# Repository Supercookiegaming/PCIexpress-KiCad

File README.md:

# PCIexpress-KiCad
PCI Express™ libraries and templates for KiCad
Made using guidelines from PCI Express™ Card Electromechanical Specification Rev. 4.0 Version 0.9 and PCI Express™ M.2 Specification Revision 1.0

Updated for KiCad 9.0.1

### Contents
**Templates:**
* M.2 A Key 22/30mm width, 30/42/60/80/110mm length
* M.2 B Key 22/30mm width, 30/42/60/80/110mm length
* M.2 M Key 22/30mm width, 30/42/60/80/110mm length
* M.2 E Key 22/30mm width, 30/42/60/80/110mm length
* M.2 A+E Key 22/30mm width, 30/42/60/80/110mm length
* M.2 B+M Key 22/30mm width, 30/42/60/80/110mm length
* x1 cards: full size, half length, low profile
* x2 cards: full size, half length, low profile
* x4 cards: full size, half length, low profile
* x8 cards: full size, half length, low profile
* x16 cards: full size, half length, low profile

**Symbols:**
* A Key M.2
* B Key M.2
* C Key M.2
* D Key M.2
* E Key M.2
* F Key M.2
* G Key M.2
* H Key M.2
* J Key M.2
* K Key M.2
* L Key M.2
* M Key M.2
* A+E Key M.2
* B+M Key M.2
* x1
* x2
* x4
* x8
* x16
* Bracket

**Footprints:**
* A Key M.2 with multiple card outlines
* B Key M.2 with multiple card outlines
* C Key M.2 with multiple card outlines
* D Key M.2 with multiple card outlines
* E Key M.2 with multiple card outlines
* F Key M.2 with multiple card outlines
* G Key M.2 with multiple card outlines
* H Key M.2 with multiple card outlines
* J Key M.2 with multiple card outlines
* K Key M.2 with multiple card outlines
* L Key M.2 with multiple card outlines
* M Key M.2 with multiple card outlines
* A+E Key M.2 with multiple card outlines
* B+M Key M.2 with multiple card outlines
* M.2 Mounting Pad
* x1 with multiple card outlines
* x2 with multiple card outlines
* x4 with multiple card outlines
* x8 with multiple card outlines
* x16 with multiple card outlines
* Full height bracket (with 3D model)
* Low profile bracket (with 3D model)
* Low profile to full height adapter bracker (with 3D model)

**Notes:**
* Transmit and Recieve pairs on M.2 Symbols are from the perspective of module not the host.
* Transmit and Recieve pairs on PCIe symbols are from the perspective of module not the host. 
* Triple check the pinout on your specific M.2 socket to ensure correct wiring.

### License
This documentation describes Open Hardware and is licensed under the CERN OHL v.1.2.

You may redistribute and modify this documentation under the terms of the CERN OHL v.1.2. (http://ohwr.org/cernohl). This documentation is distributed WITHOUT ANY EXPRESS OR IMPLIED WARRANTY, INCLUDING OF MERCHANTABILITY, SATISFACTORY QUALITY AND FITNESS FOR A PARTICULAR PURPOSE. Please see the CERN OHL v.1.2 for applicable conditions.

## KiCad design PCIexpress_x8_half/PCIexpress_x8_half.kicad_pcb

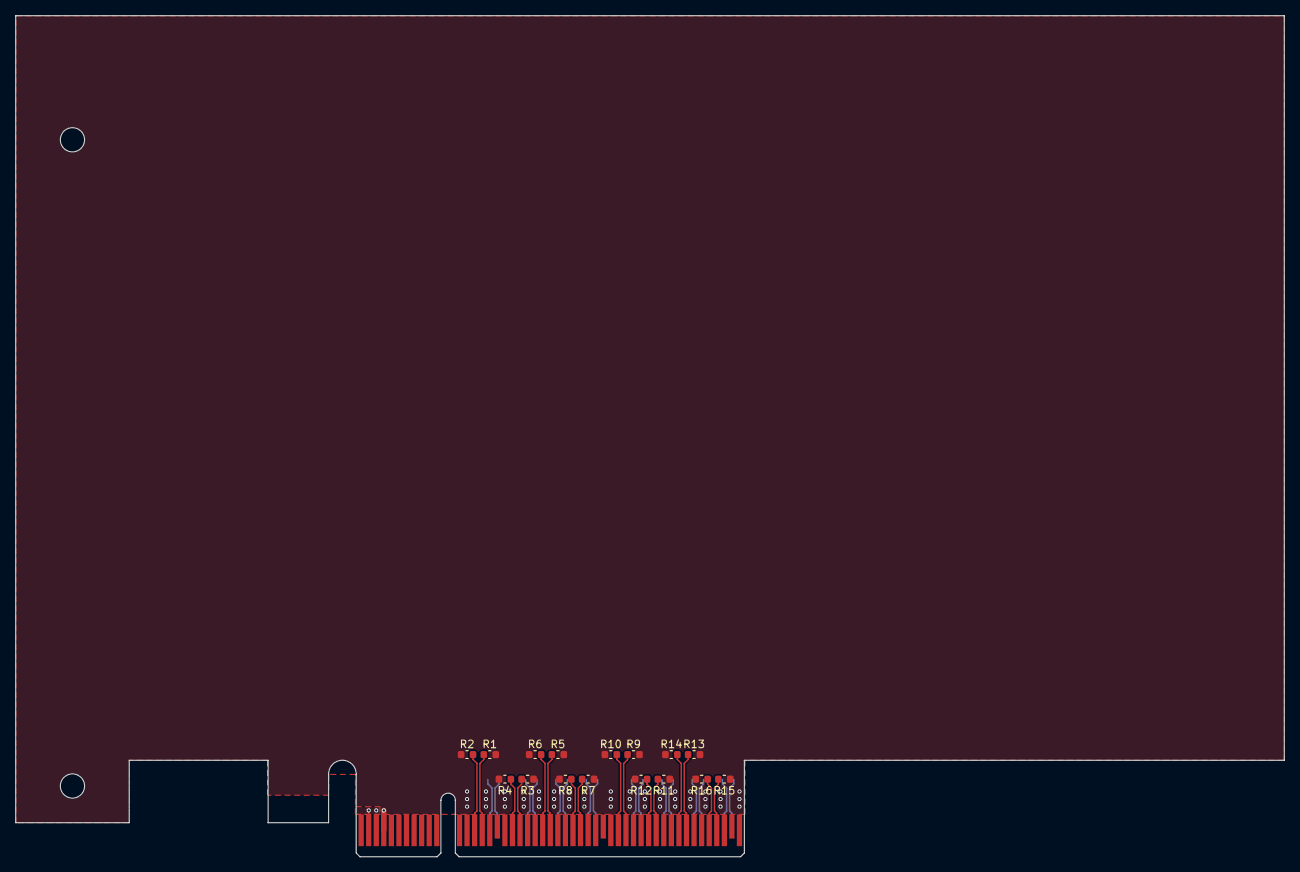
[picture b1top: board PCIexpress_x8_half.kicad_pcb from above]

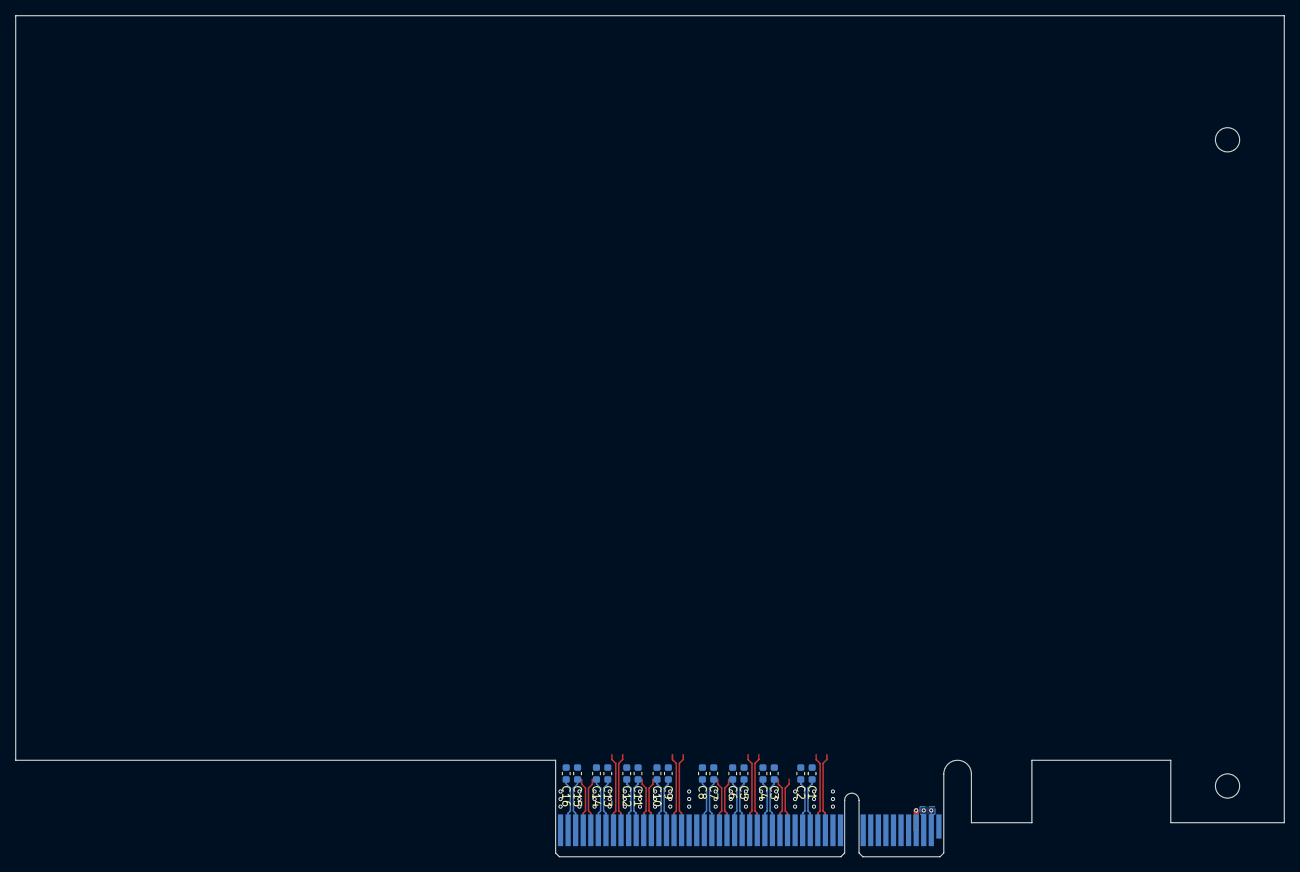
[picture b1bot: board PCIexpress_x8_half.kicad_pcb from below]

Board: 4 copper layers, 167.7 x 111.2 mm, 34 parts (16 on the bottom side), 35 nets.

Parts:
C1, C2, C3, C4, C5, C6, C7, C8, C9, C10, C11, C12, C13, C14, C15, C16: 100n; C_0603_1608Metric
J1: PCIexpress_bracket; PCIexpress_bracket_full
J2: PCIexpress_x8
R1, R2, R3, R4, R5, R6, R7, R8, R9, R10, R11, R12, R13, R14, R15, R16: 49.9; R_0603_1608Metric

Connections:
+3V3: J2.A9, J2.A10, J2.B8
+12V: J2.A2, J2.A3, J2.B1, J2.B2, J2.B3
/PCIexpress_connector/_PER0_N: C2.1, J2.A17
/PCIexpress_connector/_PER0_P: C1.2, J2.A16
/PCIexpress_connector/_PER1_N: C4.1, J2.A22
/PCIexpress_connector/_PER1_P: C3.2, J2.A21
/PCIexpress_connector/_PER2_N: C6.1, J2.A26
/PCIexpress_connector/_PER2_P: C5.2, J2.A25
/PCIexpress_connector/_PER3_N: C8.1, J2.A30
/PCIexpress_connector/_PER3_P: C7.2, J2.A29
/PCIexpress_connector/_PER4_N: C10.1, J2.A36
/PCIexpress_connector/_PER4_P: C9.2, J2.A35
/PCIexpress_connector/_PER5_N: C12.1, J2.A40
/PCIexpress_connector/_PER5_P: C11.2, J2.A39
/PCIexpress_connector/_PER6_N: C14.1, J2.A44
/PCIexpress_connector/_PER6_P: C13.2, J2.A43
/PCIexpress_connector/_PER7_N: C16.1, J2.A48
/PCIexpress_connector/_PER7_P: C15.2, J2.A47
/PET0_N: J2.B15, R1.1
/PET0_P: J2.B14, R2.1
/PET1_N: J2.B20, R3.1
/PET1_P: J2.B19, R4.1
/PET2_N: J2.B24, R5.1
/PET2_P: J2.B23, R6.1
/PET3_N: J2.B28, R7.1
/PET3_P: J2.B27, R8.1
/PET4_N: J2.B34, R9.1
/PET4_P: J2.B33, R10.1
/PET5_N: J2.B38, R11.1
/PET5_P: J2.B37, R12.1
/PET6_N: J2.B42, R13.1
/PET6_P: J2.B41, R14.1
/PET7_N: J2.B46, R15.1
/PET7_P: J2.B45, R16.1
GND: J2.A4, J2.A12, J2.A15, J2.A18, J2.A20, J2.A23, J2.A24, J2.A27, J2.A28, J2.A31, J2.A34, J2.A37, J2.A38, J2.A41, J2.A42, J2.A45, J2.A46, J2.A49, J2.B4, J2.B7, J2.B13, J2.B16, J2.B18, J2.B21, J2.B22, J2.B25, J2.B26, J2.B29, J2.B32, J2.B35, J2.B36, J2.B39, J2.B40, J2.B43, J2.B44, J2.B47, J2.B49, R1.2, R2.2, R3.2, R4.2, R5.2, R6.2, R7.2, R8.2, R9.2, R10.2, R11.2, R12.2, R13.2, R14.2, R15.2, R16.2

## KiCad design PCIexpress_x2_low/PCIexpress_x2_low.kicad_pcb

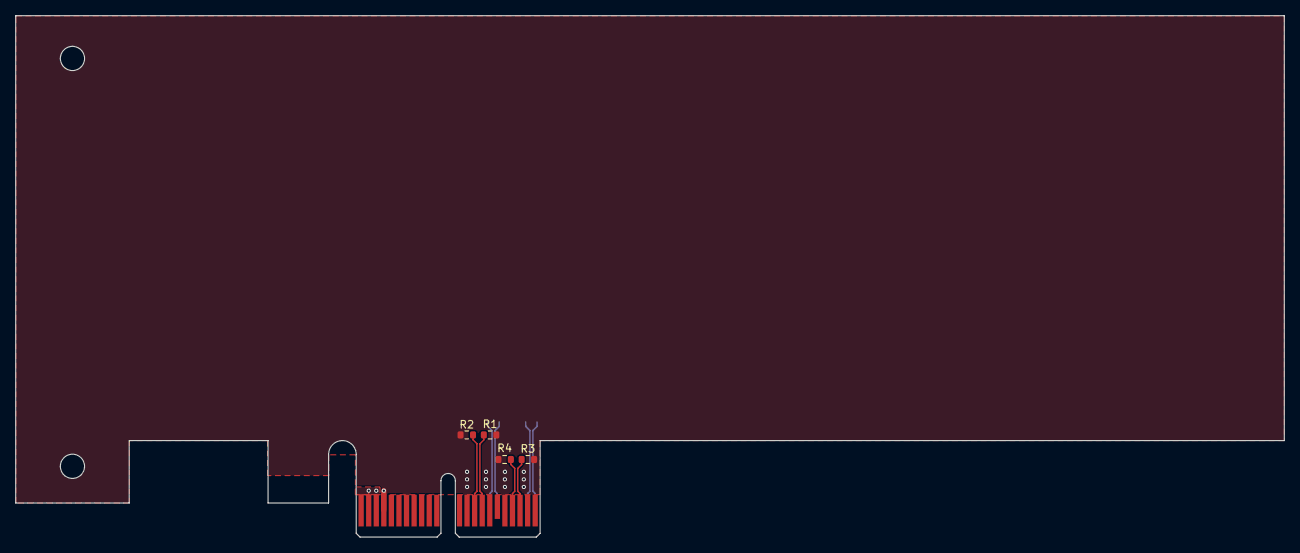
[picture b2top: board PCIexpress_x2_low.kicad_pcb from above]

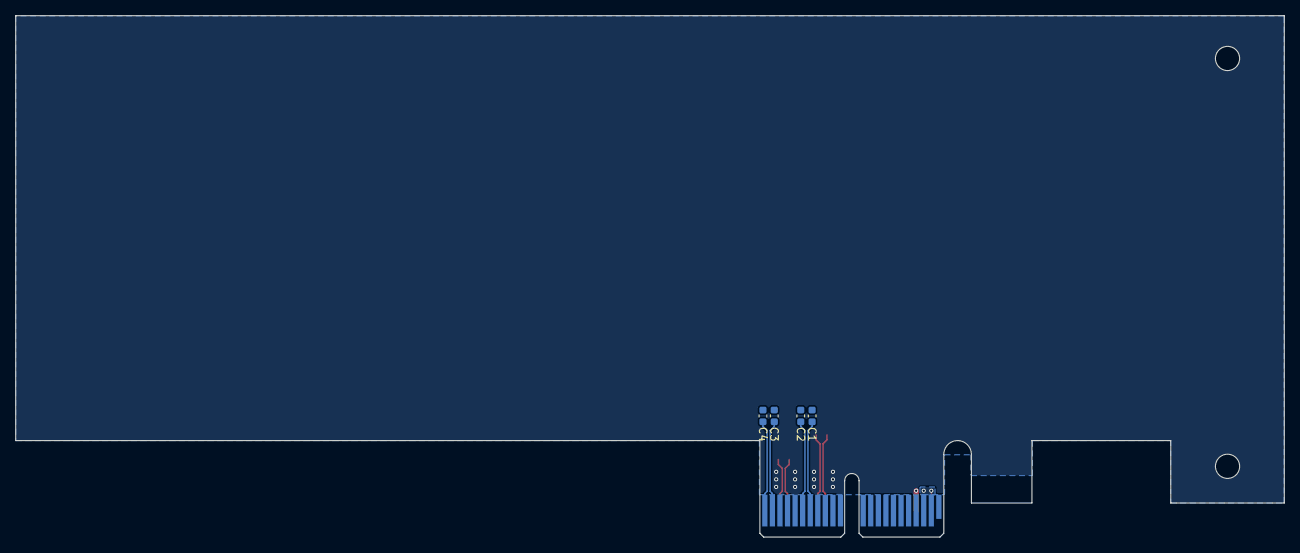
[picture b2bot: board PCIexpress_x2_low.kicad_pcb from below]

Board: 4 copper layers, 167.7 x 68.9 mm, 10 parts (4 on the bottom side), 11 nets.

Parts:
C1, C2, C3, C4: 100n; C_0603_1608Metric
J1: PCIexpress_bracket; PCIexpress_bracket_low
J1#2: PCIexpress_x2
R1, R2, R3, R4: 49.9; R_0603_1608Metric

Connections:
+3V3: J1#2.A9 (+3.3V), J1#2.A10 (+3.3V), J1#2.B8 (+3.3V)
+12V: J1#2.A2 (+12V), J1#2.A3 (+12V), J1#2.B1 (+12V), J1#2.B2 (+12V), J1#2.B3 (+12V)
/PCIexpress_connector/_PER0_N: C2.1, J1#2.A17 (PERn0)
/PCIexpress_connector/_PER0_P: C1.2, J1#2.A16 (PERp0)
/PCIexpress_connector/_PER1_N: C4.1, J1#2.A22 (PERn1)
/PCIexpress_connector/_PER1_P: C3.2, J1#2.A21 (PERp1)
/PET0_N: J1#2.B15 (PETn0), R1.1
/PET0_P: J1#2.B14 (PETp0), R2.1
/PET1_N: J1#2.B20 (PETn1), R3.1
/PET1_P: J1#2.B19 (PETp1), R4.1
GND: J1#2.A4 (GND), J1#2.A12 (GND), J1#2.A15 (GND), J1#2.A18 (GND), J1#2.A20 (GND), J1#2.B4 (GND), J1#2.B7 (GND), J1#2.B13 (GND), J1#2.B16 (GND), J1#2.B18 (GND), J1#2.B21 (GND), J1#2.B22 (GND), R1.2, R2.2, R3.2, R4.2

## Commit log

2025-05-18 Added x2
    added x2 cards
    updated for KiCad 9
2025-05-18 Updated file structure
    -Removed Backup Files
    -Removed .kicad_prl Files
    -Updated meta.html Files
    -Moved Example Cards into Templates folder to stop KiCad from giving a template error for the Library folder
2025-06-07 Added M.2 PCB Footprints
    -added M.2 Edge Connector Footprints
    -added M.2 Mounting Pad Footprint
2025-06-07 Added Symbols for M.2 Module
    -Added symbols for all m.2 keys. tx and rx are from the perspective of the m.2 module not the host device.
    -updated pcb footprints with better notes
2025-06-07 removed extra files
2025-06-07 Setup M.2 Template File Structure
    -setup file structure for A, B, E, A+E, B+M templates at all sizes
2025-06-07 Updated Template File Structure
    -grouped templated by connector type folders
2025-06-08 Finished A Key Templates
    -Added A Key Templates
    -Fixed Name mistakes in symbols
    -changed M.2 footprint to have 90 degree thermal relief pads instead of 45 degrees. 45 degrees caused no connections to copper pours.
2025-06-08 Added AC Cap note to A Key Templates
    added note about AC coupling caps for diff signals on the a key templates
2025-06-11 Added M Key Templates
    -added M key templates for all sized
    -corrected M Key symbol pinout
    -changed m.2 board thickness for A & M Key Templates
2025-06-13 Added B Key Templates
    -added B key Templates for all sizes
    -corrected B key symbol pinout
2025-06-13 added B+M key templates
    added B+M key templates in all sizes
2025-06-13 Added E Key Templates
    -added E key templates for all sizes
    -updated E Key symbol pinout
2025-06-13 Added A+E Key Templates
    added A+E key templates for all sizes
2025-06-13 Updated M. Footprints
    -removed extra drawings from footprints
    -added pcb thickness and keepout notes
    -fixed keepout area rules from marking the m.2 pads as a violation
    -updated all m.2 templates to have new footprints.
2025-06-19 Updated A+E Key Footprint
    updated A+E Key footprints to remove extra lines and updated their templates
2025-06-19 Updating PCIe Symbols
    updated the PET/PER pins on the pcie symbols
    changed the pin type for power and pci signal pins
2025-06-20 Updated PCIe Symbols
    fixed pins on all PCIe Symbols input and output are the perspective of the card.
2025-08-01 updated names on symbols
    updated the "Value" field in the m.2 symbols so the name of the connector is shown in your schematic.
    updated a few templates with new m.2 symbols
2025-08-07 updated all footprints
    added allow soldermask bridge option so DRC would not flag errors for different signals existing on the connector
    set all pad types to edge connector
    set m.2 mounting hole to a solid connection
